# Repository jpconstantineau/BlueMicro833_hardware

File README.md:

# BlueMicro833

### What is BlueMicro833?

BlueMicro833 is a nRF52833 breakout board with the form factor of an Arduino Pro Micro

### Hardware License

Design of BlueMicro833 is licensed under **CERN Open Hardware Licence Version 2 - Weakly Reciprocal**

See license.txt for more details. See this [FAQ](https://ohwr.org/project/cernohl/wikis/faq#q-copyright-does-not-cover-hardware-how-do-you-implement-strongly-reciprocal-licensing-in-cern-ohl-s) for more information on this license.

### Licenses from reference material and libraries

|  Item  | Description | Source  | License  |
|----|----      | :-----  | :-------- |
| kicad libraries | Core libraries from Kicad | [link](https://www.kicad.org/libraries/license/) | CC-BY-SA 4.0 (with exception)|
| kicad libraries | switch symbols and footprints | [link](https://github.com/sszczep/kicad-libraries)| MIT | 

### openmoko-usb-oui application details

[USB PID Request](https://github.com/openmoko/openmoko-usb-oui)

1. (done) Have a README[.txt|.md] file describing which part is under which license this will help to quickly identify the project's license, particularly when several licenses are combined, or your are using libraries under other licenses. Also make sure the combination is allowed by the individual licenses.
2. (done) Include all full text licenses in a LICENSE[.txt] file
3. (done) Include a copyright notice in the schematic sheet(s), including author and date this will determine who the copyright holder is, and when the copyright will expire.
4. (done) Include the license name in the schematic sheet(s) this becomes important when different license are combined, and parts of the project, or libraries, are under different licenses
5. () Include all schematic symbols and board footprint libraries in the project without that the project can't be seen as complete. Also ensure their license is compatible.
66. (done) Export the schematic capture as pdf, and board layout as gerber+NC drill [and other fabrication output] files - not every user can, or wants, to install the EDA suite you are using. This is even more important if in the future this suite stops supporting the current format. If you don't want to mix the fabrication output with the source files, have a general project page pointing to the source files and fabrication output.

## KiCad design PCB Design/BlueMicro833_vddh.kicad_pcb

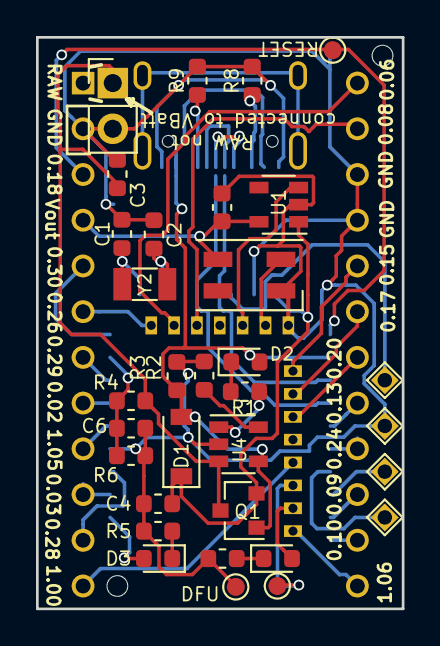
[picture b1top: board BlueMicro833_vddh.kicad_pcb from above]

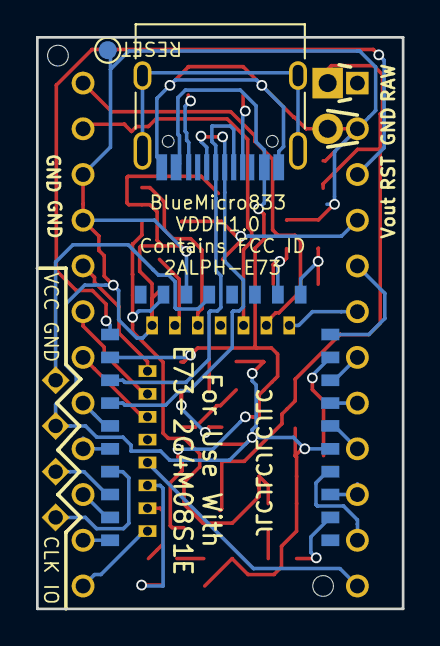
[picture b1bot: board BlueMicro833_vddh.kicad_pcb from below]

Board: 2 copper layers, 20.3 x 31.7 mm, 38 parts (3 on the bottom side), 44 nets.

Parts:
C1, C2: 22pF; C_0603_1608Metric
C3, C4, C5: 10uF; C_0603_1608Metric
C6: 1nF; C_0603_1608Metric
D1: B5819W; D_SOD-123
D2: 19-217/GHC-YR1S2/3T; LED_0603_1608Metric
D3: 19-217/BHC-ZL1M2RY/3T; LED_0603_1608Metric
D4: KT-0603R; LED_0603_1608Metric
D5: WS2812B; LED_SK6812MINI_PLCC4_3.5x3.5mm_P1.75mm
H1, H2: MountingHole; PCBA Hole
J2: Conn_01x02_Male; PinHeader_1x02_P2.54mm_Vertical
J3: DNP; USB_C_Receptacle_HRO_TYPE-C-31-M-12
Q1: SI2301CDS-T1-GE3; SOT-23
R1, R5, R7: 1K; R_0603_1608Metric
R2: 10K; R_0603_1608Metric
R3: 100K; R_0603_1608Metric
R4: 806k; R_0603_1608Metric
R6: 2M; R_0603_1608Metric
R8, R9: 5k1; R_0603_1608Metric
TP1, TP2, TP7, TP8: TestPoint_Probe; TestPoint_Pad_D1.0mm
TP3, TP4, TP5, TP6: TestPoint_Probe; TestPoint_THTPad_1.1x1.1mm_Drill0.8mm
U1: AP2139K-3.3TRG1; SOT-23-5
U2: ProMicro; pro_micro
U4: TP4054ST; SOT-23-5
U5: E73-2G4M08S1E; E73-2G4M08S1C-52840
Y2: 32,768; Crystal_SMD_3215-2Pin_3.2x1.5mm

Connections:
/P0.02: U2.8, U5.7
/P0.03: U2.10, U5.3
/P0.06: U2.13, U5.14
/P0.07: D5.4, U5.22
/P0.08: U2.14, U5.16
/P0.09: U2.22, U5.41
/P0.10: U2.23, U5.43
/P0.13: U2.20, U5.33
/P0.15: U2.17, U5.28
/P0.17: U2.18, U5.30
/P0.20: U2.19, U5.32
/P0.24: U2.21, U5.35
/P0.26: U2.6, U5.12
/P0.28: U2.11, U5.4
/P0.29: U2.7, U5.8
/P0.30: U2.5, U5.10
/P0.31: C6.1, R4.2, R6.1, U5.9
/P1.05: U2.9, U5.6
/P1.06: U2.24, U5.42
BLUE_LED: D3.2, U5.2
DATA+: J3.A6, J3.B6, U5.31
DATA-: J3.A7, J3.B7, U5.29
DFU: TP1.1, U5.38
GND: C1.2, C2.1, C3.2, C4.2, C5.2, C6.2, D5.3, J2.2, J3.A1, J3.A12, J3.B1, J3.B12, R2.2, R3.2, R5.2, R6.2, R7.2, R8.2, R9.2, TP2.1, TP6.1, TP8.1, U1.2, U2.2, U2.15, U2.16, U4.2, U5.5, U5.21, U5.24
unnamed: C1.1, U5.11, Y2.1
unnamed: C2.2, U5.13, Y2.2
unnamed: D2.1, R1.1
unnamed: D3.1, R5.1
unnamed: D4.1, R7.1
unnamed: J3.A5, R9.1
unnamed: J3.B5, R8.1
unnamed: R1.2, U4.1
unnamed: R2.1, U4.5
RED_LED: D4.2, U5.40
RESET: TP7.1, U2.3, U5.26
SWCLK: TP3.1, U5.39
SWDIO: TP4.1, U5.37
SWO: U2.12, U5.36
VBAT: C3.1, J2.1, Q1.3, R4.1, U4.3
VBUS: D1.2, D2.2, J3.A4, J3.A9, J3.B4, J3.B9, Q1.1, R3.1, U4.4, U5.27
VCC: TP5.1, U5.19
Venable: U1.3, U5.20
Vin: C4.1, D1.1, Q1.2, U1.1, U5.23
Vout: C5.1, D5.1, U1.5, U2.4

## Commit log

2023-06-01 Update README.md
    Closes #2
